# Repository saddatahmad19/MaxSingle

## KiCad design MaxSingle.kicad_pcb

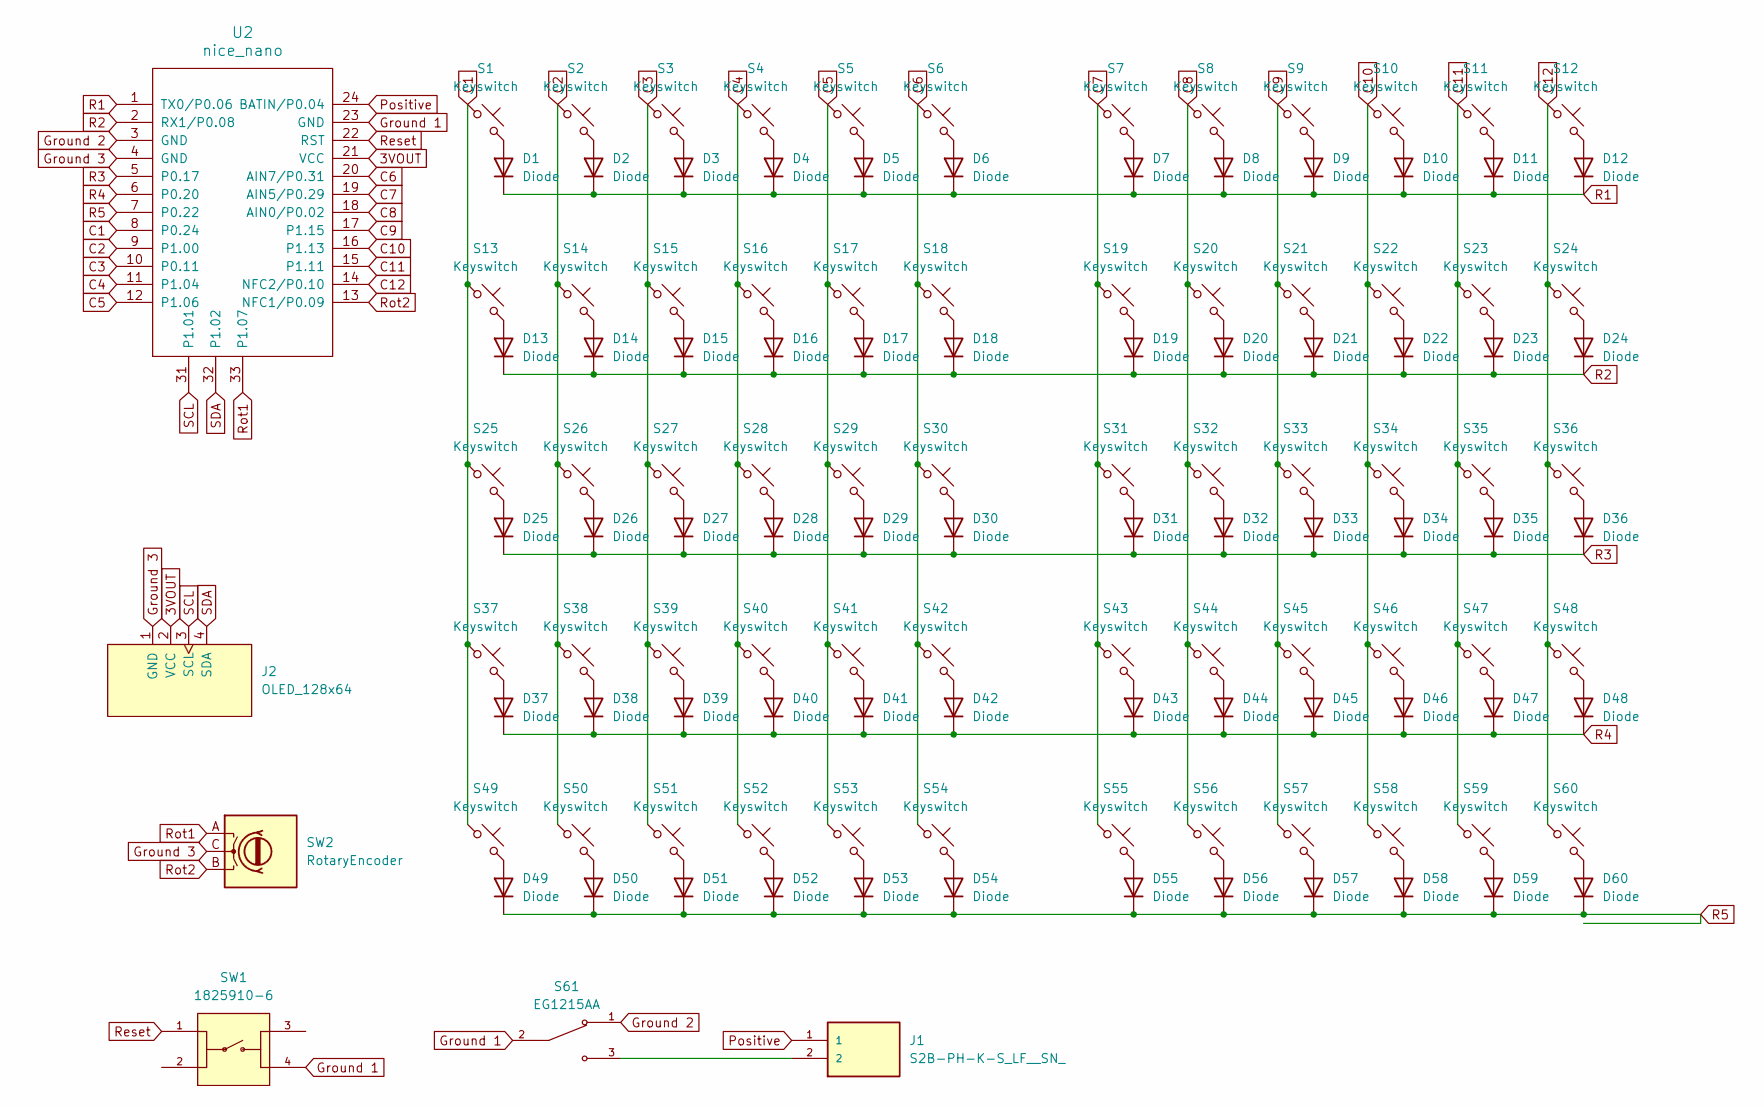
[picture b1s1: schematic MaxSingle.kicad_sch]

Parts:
D1, D2, D3, D4, D5, D6, D7, D8, D9, D10, D11, D12, D13, D14, D15, D16, D17, D18, D19, D20, D21, D22, D23, D24, D25, D26, D27, D28, D29, D30, D31, D32, D33, D34, D35, D36, D37, D38, D39, D40, D41, D42, D43, D44, D45, D46, D47, D48, D49, D50, D51, D52, D53, D54, D55, D56, D57, D58, D59, D60: Diode; Diode_SOD-123
J1: S2B-PH-K-S_LF__SN_; JST_S2B-PH-K-S_LF__SN_
J2: OLED_128x64
S1, S2, S3, S4, S5, S6, S7, S8, S9, S10, S11, S12, S13, S14, S15, S16, S17, S18, S19, S20, S21, S22, S23, S24, S25, S26, S27, S28, S29, S30, S31, S32, S33, S34, S35, S36, S37, S38, S39, S40, S41, S42, S43, S44, S45, S46, S47, S48, S49, S50, S51, S52, S53, S56, S57, S58, S59, S60: Keyswitch; Hotswap_MX_Plated_1.00u
S54, S55: Keyswitch; Hotswap_MX_Plated_1.25u_90deg
S61: EG1215AA; SW_EG1215AA; PARTREV A
SW1: 1825910-6; SW_1825910-6-4; PARTREV C10
SW2: RotaryEncoder; RotaryEncoder_Alps_EC11E_Vertical_H20mm
U2: nice_nano

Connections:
3VOUT: J2.2 (VCC), U2.21 (VCC)
C1: S1.1, S13.1, S25.1, S37.1, S49.1, U2.8 (P0.24)
C2: S2.1, S14.1, S26.1, S38.1, S50.1, U2.9 (P1.00)
C3: S3.1, S15.1, S27.1, S39.1, S51.1, U2.10 (P0.11)
C4: S4.1, S16.1, S28.1, S40.1, S52.1, U2.11 (P1.04)
C5: S5.1, S17.1, S29.1, S41.1, S53.1, U2.12 (P1.06)
C6: S6.1, S18.1, S30.1, S42.1, S54.1, U2.20 (AIN7/P0.31)
C7: S7.1, S19.1, S31.1, S43.1, S55.1, U2.19 (AIN5/P0.29)
C8: S8.1, S20.1, S32.1, S44.1, S56.1, U2.18 (AIN0/P0.02)
C9: S9.1, S21.1, S33.1, S45.1, S57.1, U2.17 (P1.15)
C10: S10.1, S22.1, S34.1, S46.1, S58.1, U2.16 (P1.13)
C11: S11.1, S23.1, S35.1, S47.1, S59.1, U2.15 (P1.11)
C12: S12.1, S24.1, S36.1, S48.1, S60.1, U2.14 (NFC2/P0.10)
Ground 1: S61.2, SW1.4, U2.23 (GND)
Ground 2: S61.1, U2.3 (GND)
Ground 3: J2.1 (GND), SW2.C, U2.4 (GND)
unnamed: D1.2 (A), S1.2
unnamed: D2.2 (A), S2.2
unnamed: D3.2 (A), S3.2
unnamed: D4.2 (A), S4.2
unnamed: D5.2 (A), S5.2
unnamed: D6.2 (A), S6.2
unnamed: D7.2 (A), S7.2
unnamed: D8.2 (A), S8.2
unnamed: D9.2 (A), S9.2
unnamed: D10.2 (A), S10.2
unnamed: D11.2 (A), S11.2
unnamed: D12.2 (A), S12.2
unnamed: D13.2 (A), S13.2
unnamed: D14.2 (A), S14.2
unnamed: D15.2 (A), S15.2
unnamed: D16.2 (A), S16.2
unnamed: D17.2 (A), S17.2
unnamed: D18.2 (A), S18.2
unnamed: D19.2 (A), S19.2
unnamed: D20.2 (A), S20.2
unnamed: D21.2 (A), S21.2
unnamed: D22.2 (A), S22.2
unnamed: D23.2 (A), S23.2
unnamed: D24.2 (A), S24.2
unnamed: D25.2 (A), S25.2
unnamed: D26.2 (A), S26.2
unnamed: D27.2 (A), S27.2
unnamed: D28.2 (A), S28.2
unnamed: D29.2 (A), S29.2
unnamed: D30.2 (A), S30.2
unnamed: D31.2 (A), S31.2
unnamed: D32.2 (A), S32.2
unnamed: D33.2 (A), S33.2
unnamed: D34.2 (A), S34.2
unnamed: D35.2 (A), S35.2
unnamed: D36.2 (A), S36.2
unnamed: D37.2 (A), S37.2
unnamed: D38.2 (A), S38.2
unnamed: D39.2 (A), S39.2
unnamed: D40.2 (A), S40.2
unnamed: D41.2 (A), S41.2
unnamed: D42.2 (A), S42.2
unnamed: D43.2 (A), S43.2
unnamed: D44.2 (A), S44.2
unnamed: D45.2 (A), S45.2
unnamed: D46.2 (A), S46.2
unnamed: D47.2 (A), S47.2
unnamed: D48.2 (A), S48.2
unnamed: D49.2 (A), S49.2
unnamed: D50.2 (A), S50.2
unnamed: D51.2 (A), S51.2
unnamed: D52.2 (A), S52.2
unnamed: D53.2 (A), S53.2
unnamed: D54.2 (A), S54.2
unnamed: D55.2 (A), S55.2
unnamed: D56.2 (A), S56.2
unnamed: D57.2 (A), S57.2
unnamed: D58.2 (A), S58.2
unnamed: D59.2 (A), S59.2
unnamed: D60.2 (A), S60.2
unnamed: J1.2, S61.3
Positive: J1.1, U2.24 (BATIN/P0.04)
R1: D1.1 (K), D2.1 (K), D3.1 (K), D4.1 (K), D5.1 (K), D6.1 (K), D7.1 (K), D8.1 (K), D9.1 (K), D10.1 (K), D11.1 (K), D12.1 (K), U2.1 (TX0/P0.06)
R2: D13.1 (K), D14.1 (K), D15.1 (K), D16.1 (K), D17.1 (K), D18.1 (K), D19.1 (K), D20.1 (K), D21.1 (K), D22.1 (K), D23.1 (K), D24.1 (K), U2.2 (RX1/P0.08)
R3: D25.1 (K), D26.1 (K), D27.1 (K), D28.1 (K), D29.1 (K), D30.1 (K), D31.1 (K), D32.1 (K), D33.1 (K), D34.1 (K), D35.1 (K), D36.1 (K), U2.5 (P0.17)
R4: D37.1 (K), D38.1 (K), D39.1 (K), D40.1 (K), D41.1 (K), D42.1 (K), D43.1 (K), D44.1 (K), D45.1 (K), D46.1 (K), D47.1 (K), D48.1 (K), U2.6 (P0.20)
R5: D49.1 (K), D50.1 (K), D51.1 (K), D52.1 (K), D53.1 (K), D54.1 (K), D55.1 (K), D56.1 (K), D57.1 (K), D58.1 (K), D59.1 (K), D60.1 (K), U2.7 (P0.22)
Reset: SW1.1, U2.22 (RST)
Rot1: SW2.A, U2.33 (P1.07)
Rot2: SW2.B, U2.13 (NFC1/P0.09)
SCL: J2.3 (SCL), U2.31 (P1.01)
SDA: J2.4 (SDA), U2.32 (P1.02)

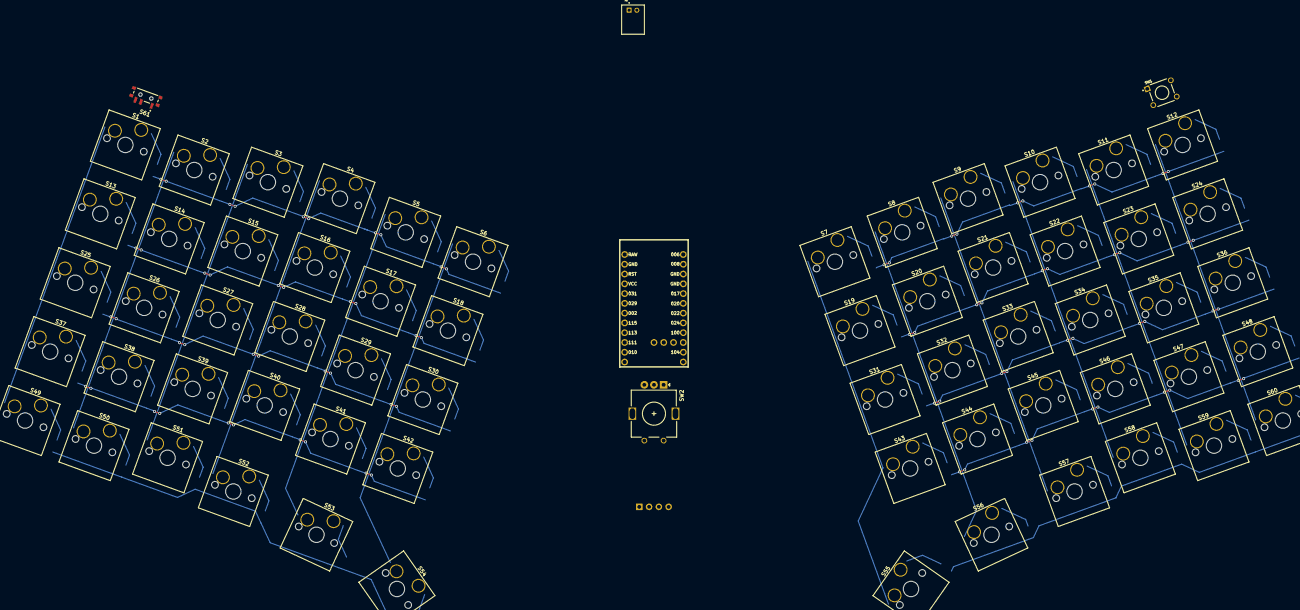
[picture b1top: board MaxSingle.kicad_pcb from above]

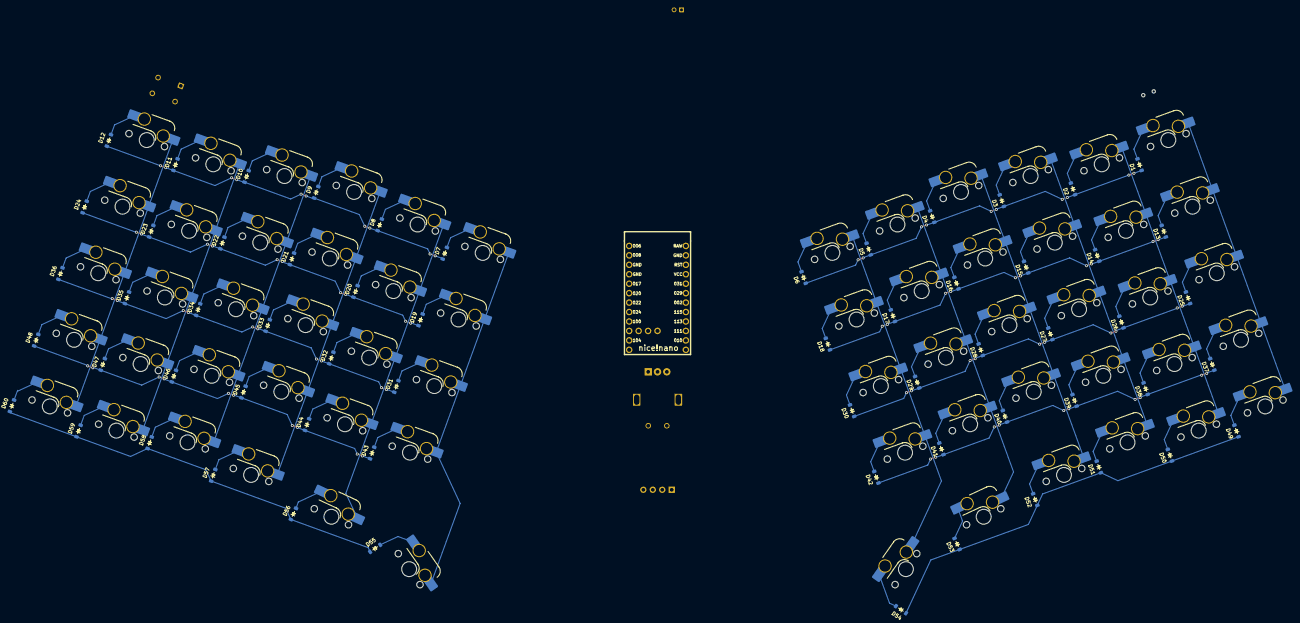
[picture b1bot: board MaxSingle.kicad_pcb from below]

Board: 2 copper layers, 126 parts (61 on the bottom side), 88 nets.

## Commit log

2024-04-14 second changes
